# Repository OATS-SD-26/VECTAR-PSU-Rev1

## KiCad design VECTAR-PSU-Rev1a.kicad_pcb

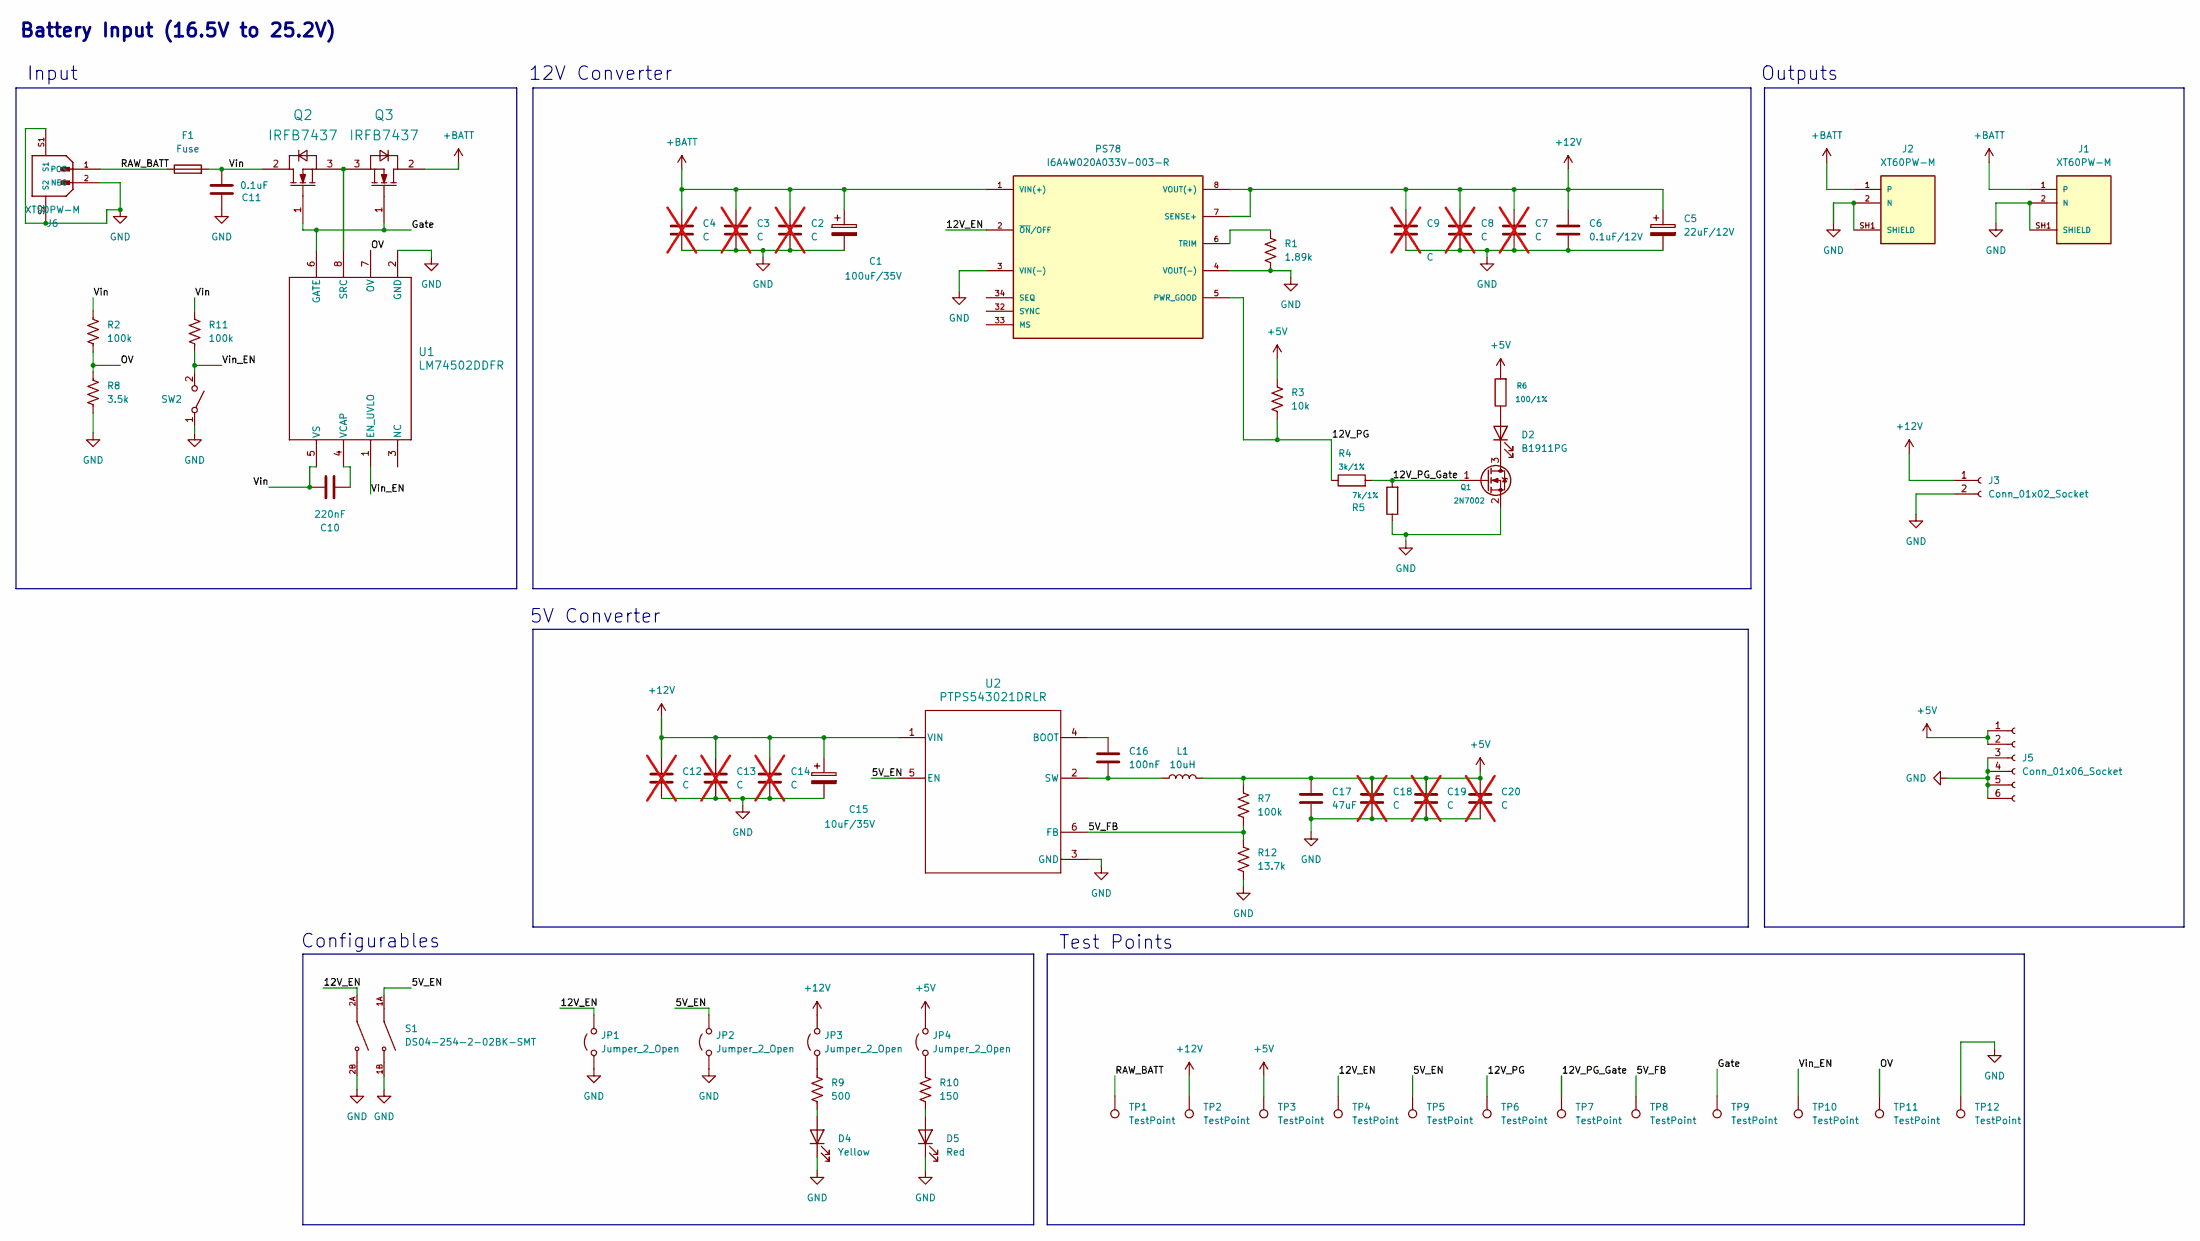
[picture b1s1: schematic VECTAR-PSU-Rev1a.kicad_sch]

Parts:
C1: 100uF/35V; EHBSA035M1010608T
C2, C3, C4, C7, C8, C9, C12, C13, C14, C18, C19, C20: C; C_0603_1608Metric; not fitted
C5: 22uF/12V; C_0805_2012Metric
C6: 0.1uF/12V; C_0603_1608Metric
C10: 220nF; C_0603_1608Metric
C11: 0.1uF; C_0603_1608Metric
C15: 10uF/35V; C_0603_1608Metric
C16: 100nF; C_0603_1608Metric
C17: 47uF; CAPAE660X600N
D2: B1911PG; LED_B1911PG--20D000514U1930_HVK
D4: Yellow; LTST_C190KSKT
D5: Red; LTST_S270KRKT
F1: Fuse; 3-140-178
J1, J2: XT60PW-M; AMASS_XT60PW-M; PARTREV 1.2
J3: Conn_01x02_Socket; Rocker-Switch
J5: Conn_01x06_Socket; 6-pin-connector
J6: XT90PW-M; AMASS_XT90PW-M; PARTREV V00
JP1, JP2, JP3, JP4: Jumper_2_Open; R_0603_1608Metric
L1: 10uH; IND_BOURNS_SDR1307
PS78: I6A4W020A033V-003-R; CONV_I6A4W020A033V-003-R; PARTREV V4; DigiKey_Part_Number 285-2669-ND
Q1: 2N7002; SOT95P240X111-3N
Q2, Q3: IRFB7437; TO254P483X1016X1944-3B
R1: 1.89k; R_0805_2012Metric
R2, R7, R11: 100k; R_0603_1608Metric
R3: 10k; R_0603_1608Metric
R4: 3k/1%; R_0603_1608Metric
R5: 7k/1%; R_0603_1608Metric
R6: 100/1%; R_0603_1608Metric
R8: 3.5k; R_0603_1608Metric
R9: 500; R_0603_1608Metric
R10: 150; R_0603_1608Metric
R12: 13.7k; R_0603_1608Metric
S1: DS04-254-2-02BK-SMT; SW_DS04-254-2-02BK-SMT; PARTREV V0.0
SW2: RA1113112R; Rocker-Switch
TP1, TP2, TP3, TP4, TP5, TP6, TP7, TP8, TP9, TP10, TP11, TP12: TestPoint; KEYSTONE_5002
U1: LM74502DDFR; DDF0008A-MFG
U2: PTPS543021DRLR; DRL0006A-MFG

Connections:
+5V: C17.1, C18.1, C19.1, C20.1, J5.1, J5.2, JP4.2 (B), L1.2, R3.1, R6.2, R7.1, TP3.1
+12V: C5.1, C6.1, C7.1, C8.1, C9.1, C12.1, C13.1, C14.1, C15.1, J3.1, JP3.2 (B), PS78.7 (SENSE+), PS78.8 (VOUT(+)), TP2.1, U2.1 (VIN)
+BATT: C1.1, C2.1, C3.1, C4.1, J1.1, J2.1, PS78.1 (VIN(+)), Q3.2 (DRAIN)
/5V_EN: JP2.2 (B), S1.1A, TP5.1, U2.5 (EN)
/5V_FB: R7.2, R12.1, TP8.1, U2.6 (FB)
/12V_EN: JP1.2 (B), PS78.2 (~ON/OFF), S1.2A, TP4.1
/12V_PG: PS78.5 (PWR_GOOD), R3.2, R4.1, TP6.1
/12V_PG_Gate: Q1.1 (G), R4.2, R5.2, TP7.1
/Gate: Q2.1 (GATE), Q3.1 (GATE), TP9.1, U1.6 (GATE)
/OV: R2.2, R8.1, TP11.1, U1.7 (OV)
/RAW_BATT: F1.1, J6.1 (POS), TP1.1
/Vin: C10.1, C11.2, F1.2, Q2.2 (DRAIN), R2.1, R11.1, U1.5 (VS)
/Vin_EN: R11.2, SW2.2 (B), TP10.1, U1.1 (EN_UVLO)
GND: C1.2, C2.2, C3.2, C4.2, C5.2, C6.2, C7.2, C8.2, C9.2, C11.1, C12.2, C13.2, C14.2, C15.2, C17.2, C18.2, C19.2, C20.2, D4.1 (K), D5.1 (K), J1.2 (N), J1.SH1 (SHIELD), J1.SH2 (SHIELD), J2.2 (N), J2.SH1 (SHIELD), J2.SH2 (SHIELD), J3.2, J5.3, J5.4, J5.5, J5.6, J6.2 (NEG), J6.S1, J6.S2, JP1.1 (A), JP2.1 (A), PS78.3 (VIN(-)), PS78.4 (VOUT(-)), Q1.2 (S), R1.2, R5.1, R8.2, R12.2, S1.1B, S1.2B, SW2.1 (A), TP12.1, U1.2 (GND), U2.3 (GND)
unnamed: D2.2 (A), R6.1
unnamed: D2.1 (K), Q1.3 (D)
unnamed: D4.2 (A), R9.2
unnamed: D5.2 (A), R10.2
unnamed: JP3.1 (A), R9.1
unnamed: JP4.1 (A), R10.1
unnamed: PS78.6 (TRIM), R1.1
unnamed: Q2.3 (SOURCE), Q3.3 (SOURCE), U1.8 (SRC)
unnamed: C10.2, U1.4 (VCAP)
unnamed: C16.1, U2.4 (BOOT)
unnamed: C16.2, L1.1, U2.2 (SW)

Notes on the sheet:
Configurables
Test Points
Battery Input (16.5V to 25.2V)
Outputs
12V Converter
5V Converter
Input

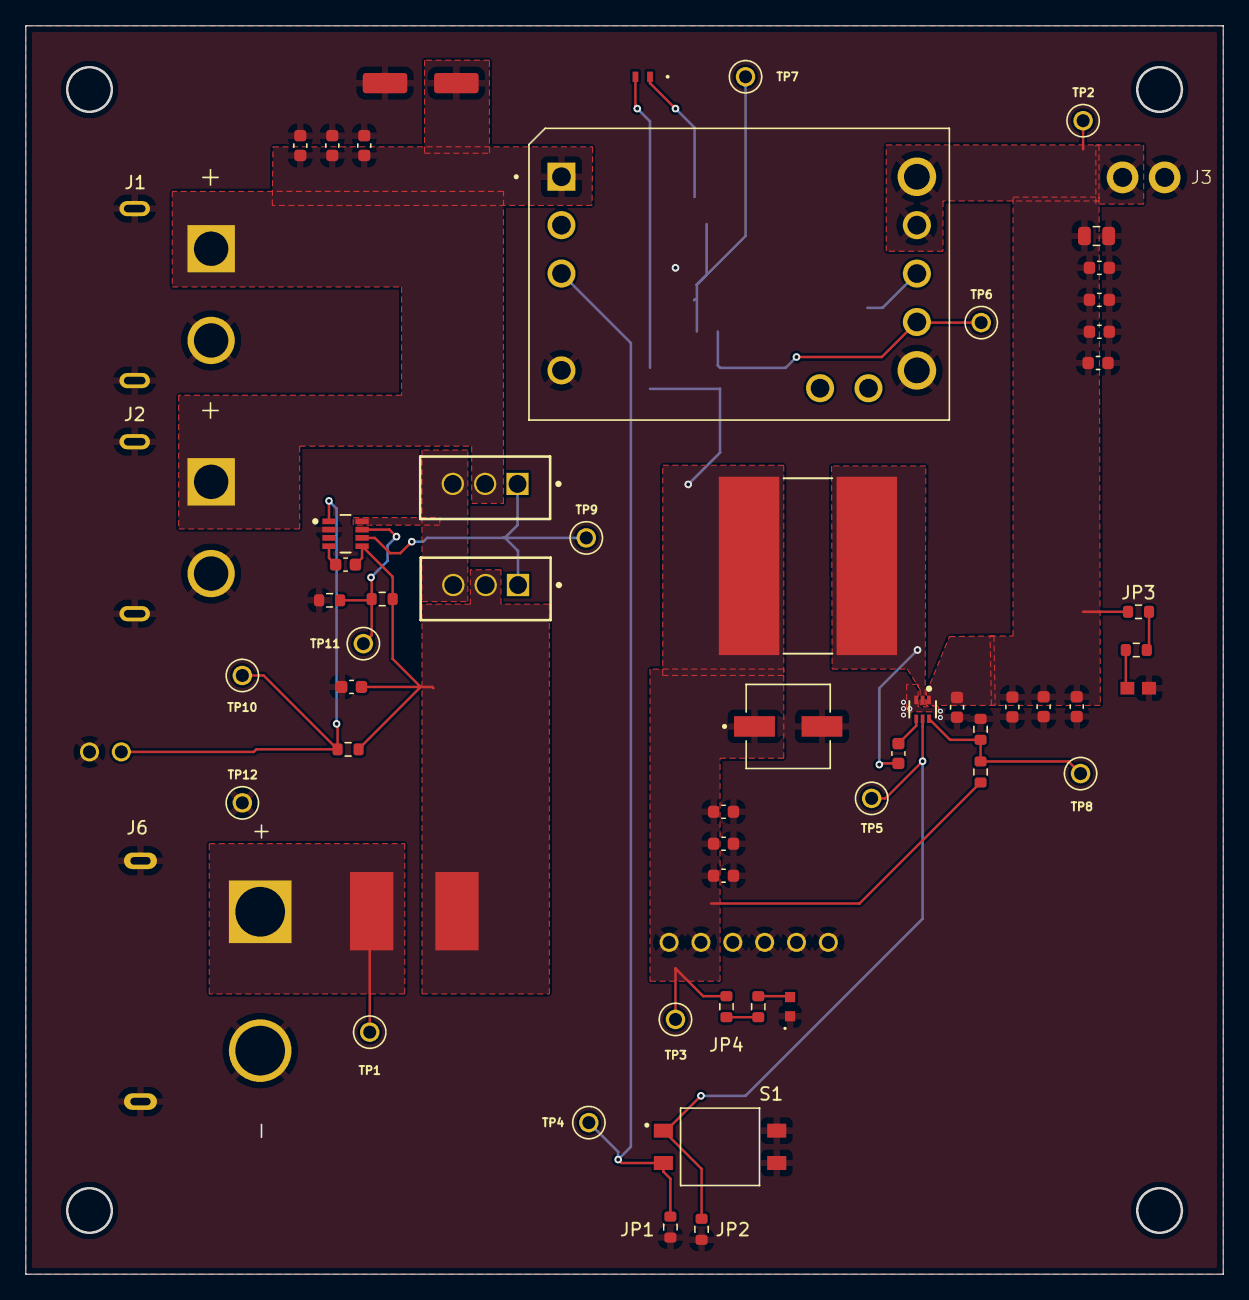
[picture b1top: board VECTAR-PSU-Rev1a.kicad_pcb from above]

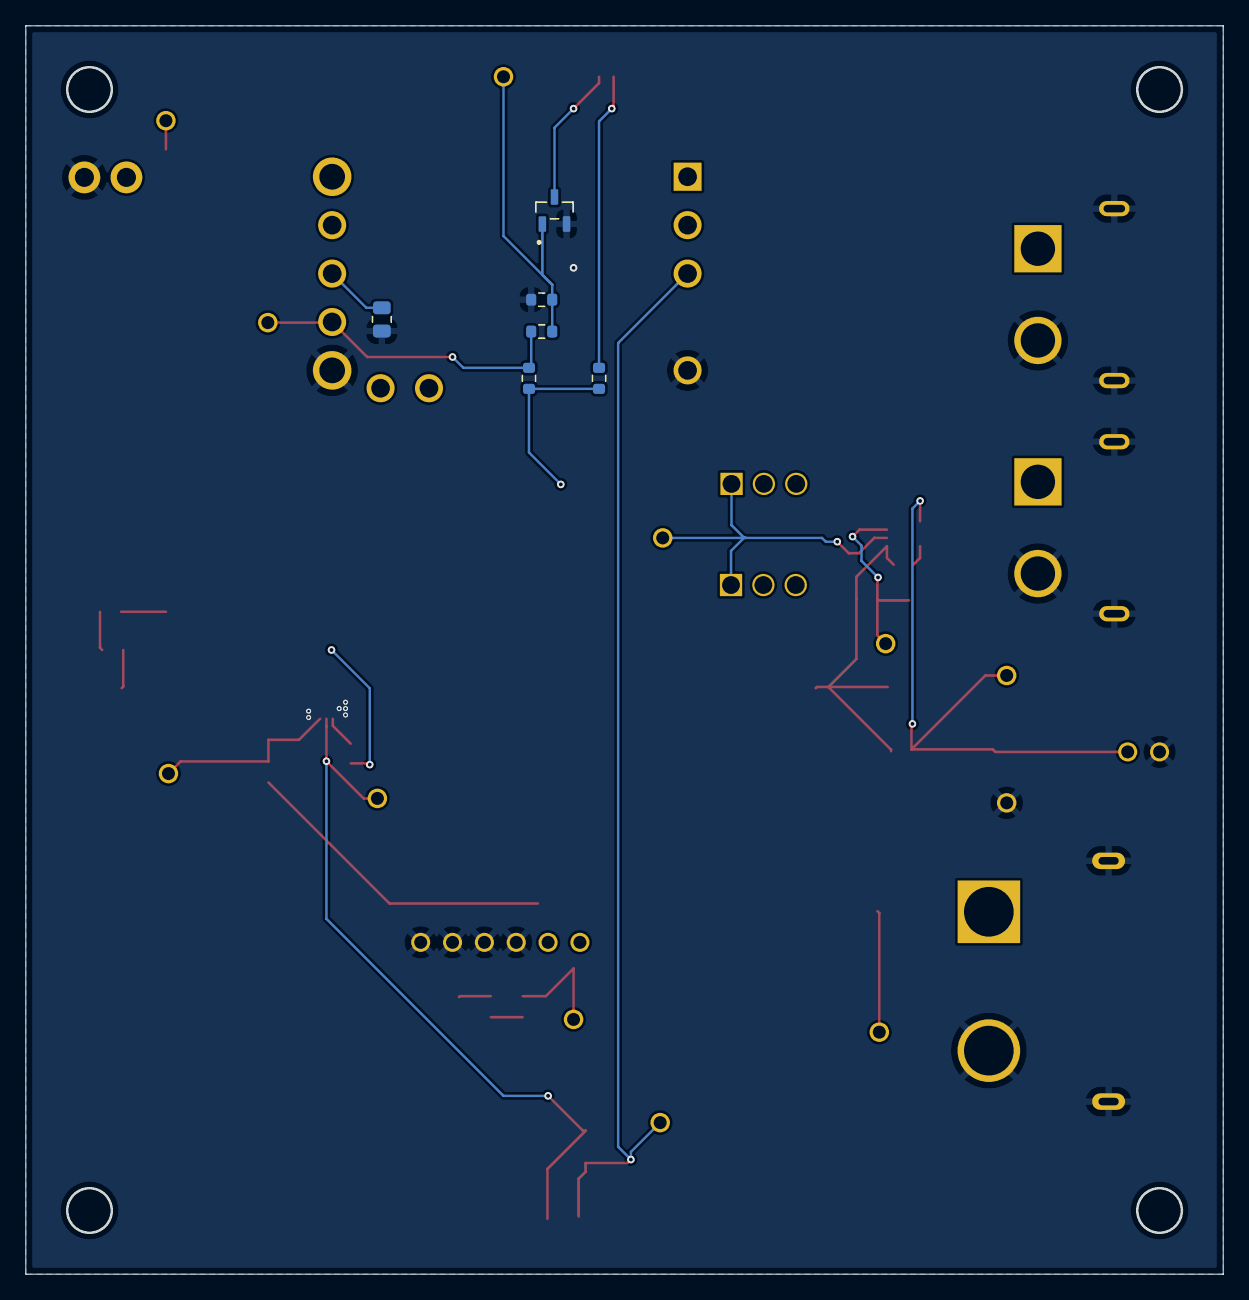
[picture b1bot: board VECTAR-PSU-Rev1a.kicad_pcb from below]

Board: 2 copper layers, 93.9 x 97.9 mm, 66 parts (6 on the bottom side), 25 nets.

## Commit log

2026-03-03 Initial Design of PSU
2026-03-08 Rev1b Design of PSU
2026-03-09 Cleaned up libraries and added some testpoints. Need to finalize PG circuit and testpoint locations
2026-03-10 updated PG circuit on 12V converter
2026-03-10 Added ideal diode controller, still not done
2026-03-10 schematic complete, adding footprints now
2026-03-12 schematic complete, layout started
2026-03-17 PCB Rev 1 Complete
2026-03-20 PCB Rev 1 Ordered
2026-05-01 final commit
